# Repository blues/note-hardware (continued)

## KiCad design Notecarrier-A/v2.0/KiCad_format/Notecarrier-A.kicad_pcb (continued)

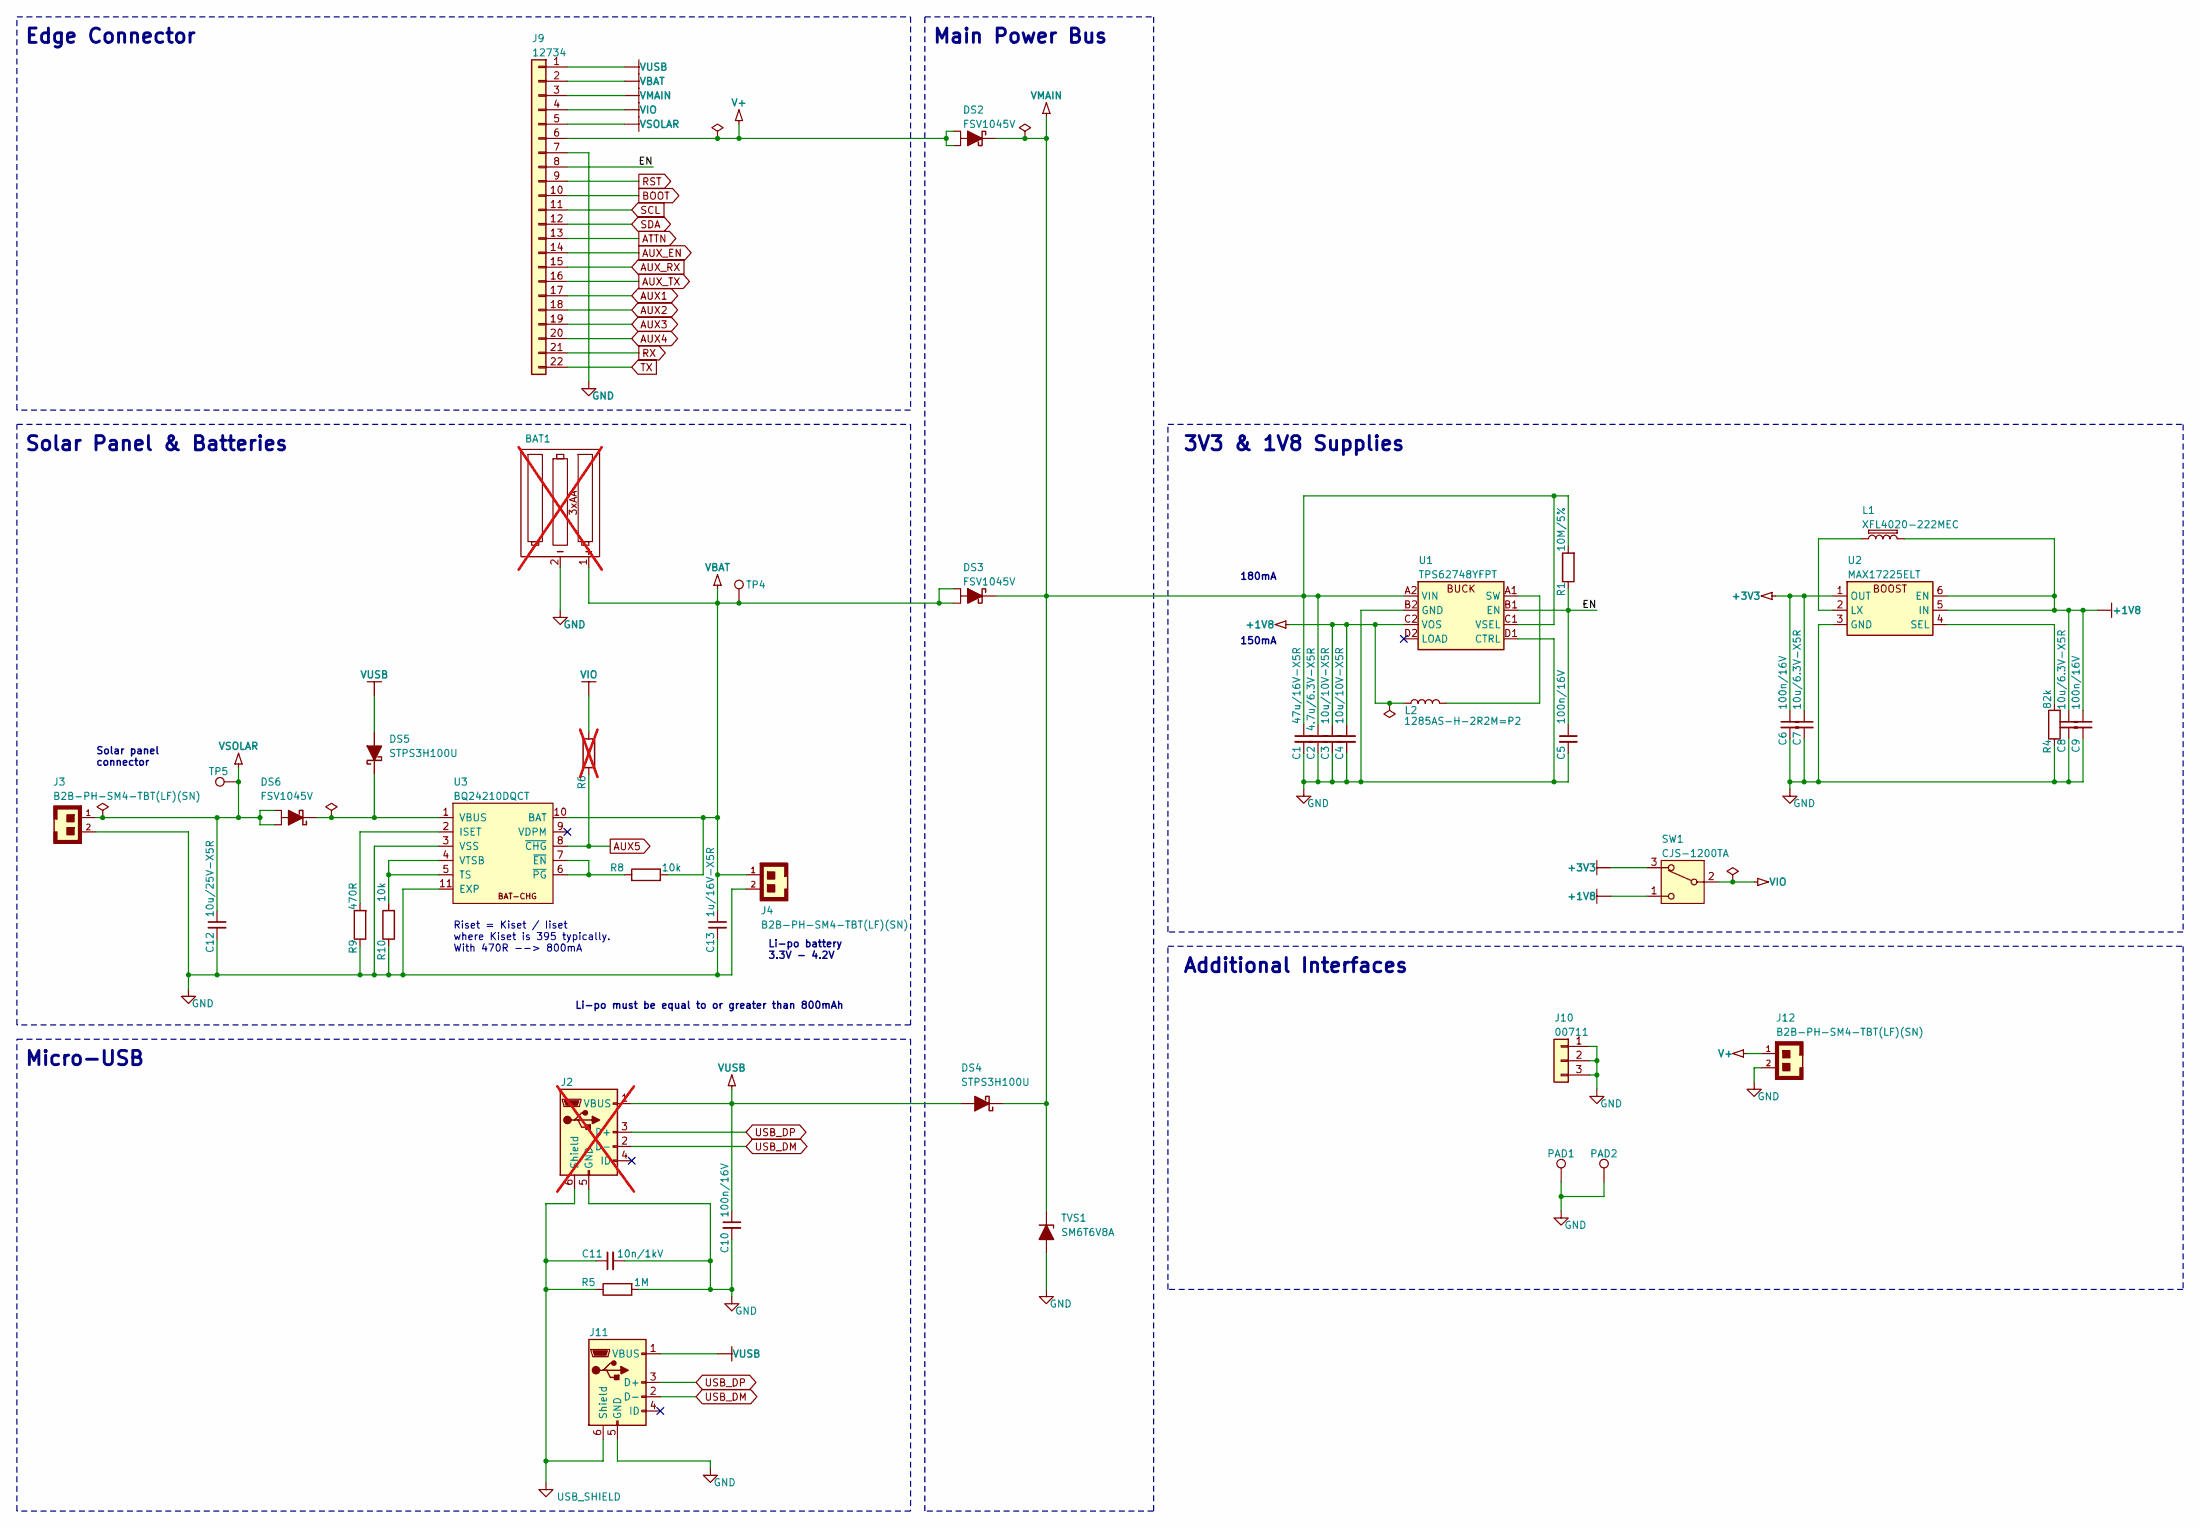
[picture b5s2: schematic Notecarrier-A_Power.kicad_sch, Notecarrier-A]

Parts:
BAT1: NU; BATHLD-2464-NO_MECH; MPN 2464; not fitted
C1: 47u/16V-X5R; CS-C-1206
C2: 4.7u/6.3V-X5R; CS-C-0402
C3, C4: 10u/10V-X5R; CS-C-0603
C5, C6, C9, C10: 100n/16V; CS-C-0402
C7, C8: 10u/6.3V-X5R; CS-C-0402
C11: 10n/1kV; CS-C-1206
C12: 10u/25V-X5R; CS-C-1206
C13: 1u/16V-X5R; CS-C-0402
DS2, DS3, DS6: FSV1045V; TO277-3; MPN FSV1045V
DS4, DS5: STPS3H100U; SMB; MPN STPS3H100U
J2: NU; J-5-0065-FDS-UUSB1051330001_NO-SILK; MPN 1051330001; not fitted
J3, J4, J12: B2B-PH-SM4-TBT(LF)(SN); J-2-0200-MDS-B2B-PH-SM4; MPN B2B-PH-SM4-TBT(LF)(SN)
J9: 12734; J-22-0254-FDT-H0508_EDGE; MPN 12734
J10: 00711; J-3-0254-FDT_H0508; MPN 00711
J11: 10118192-0002LF; J-5-0065-FOS-USB10118192-NOF; MPN 10118192-0002LF
L1: XFL4020-222MEC; LS-XFL4020; MPN XFL4020-222MEC
L2: 1285AS-H-2R2M=P2; LS-0806; MPN 1285AS-H-2R2M=P2
PAD1, PAD2: TPS; PAD-THT-CAS-0100
R1: 10M/5%; RS-0402
R4: 82k; RS-0402
R5: 1M; RS-1206
R6: NU; RS-0402; not fitted
R8, R10: 10k; RS-0402
R9: 470R; RS-0402
SW1: CJS-1200TA; SW_CJS-1200TA_NO-SILK
TP4, TP5: TPS; TPS-SPEA
TVS1: SM6T6V8A; SMB
U1: TPS62748YFPT; XFBGA8; MPN TPS62748YFPT
U2: MAX17225ELT; WDFN6-0200X0200; MPN MAX17225ELT+T
U3: BQ24210DQCT; WSON10-EXP_NO-SILK; MPN BQ24210DQCT

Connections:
+1V8: C3.1, C4.1, C8.1, C9.1, L1.2, L2.2, SW1.1 (C), U1.C2 (VOS), U2.5 (IN), U2.6 (EN)
+3V3: C6.1, C7.1, SW1.3 (A), U2.1 (OUT)
/Power/EN: C5.1, J9.8, R1.1, U1.B1 (EN)
ATTN: J9.13; also elsewhere on the board
AUX1: J9.17; also elsewhere on the board
AUX2: J9.18; also elsewhere on the board
AUX3: J9.19; also elsewhere on the board
AUX4: J9.20; also elsewhere on the board
AUX5: R6.1, U3.8 (~CHG); also elsewhere on the board
AUX_EN: J9.14; also elsewhere on the board
AUX_RX: J9.15; also elsewhere on the board
AUX_TX: J9.16; also elsewhere on the board
BOOT: J9.10; also elsewhere on the board
GND: BAT1.2 (-), C1.2, C2.2, C3.2, C4.2, C5.2, C6.2, C7.2, C8.2, C9.2, C10.2, C11.2, C12.2, C13.2, J2.5 (GND), J3.2, J4.2, J9.7, J10.1, J10.2, J10.3, J11.5 (GND), J12.2, PAD1.1, PAD2.1, R4.1, R5.2, R9.1, R10.1, TVS1.2 (A2), U1.B2 (GND), U1.D1 (CTRL), U2.3 (GND), U3.3 (VSS), U3.11 (EXP); also elsewhere on the board
unnamed: DS5.1 (K), DS6.3 (C), U3.1 (VBUS)
unnamed: C11.1, J2.6 (Shield), J11.6 (Shield), R5.1
unnamed: L2.1, U1.A1 (SW)
unnamed: L1.1, U2.2 (LX)
unnamed: R4.2, U2.4 (SEL)
unnamed: R9.2, U3.2 (ISET)
unnamed: R10.2, U3.4 (VTSB), U3.5 (TS)
unnamed: R8.1, U3.6 (~PG), U3.7 (~EN)
RST: J9.9; also elsewhere on the board
RX: J9.21; also elsewhere on the board
SCL: J9.11; also elsewhere on the board
SDA: J9.12; also elsewhere on the board
TX: J9.22; also elsewhere on the board
USB_DM: J2.2 (D-), J11.2 (D-); also elsewhere on the board
USB_DP: J2.3 (D+), J11.3 (D+); also elsewhere on the board
V+: DS2.1 (A1), DS2.2 (A2), J9.6, J12.1
VBAT: BAT1.1 (+), C13.1, DS3.1 (A1), DS3.2 (A2), J4.1, J9.2, R8.2, TP4.1, U3.10 (BAT)
VIO: J9.4, R6.2, SW1.2 (B); also elsewhere on the board
VMAIN: C1.1, C2.1, DS2.3 (C), DS3.3 (C), DS4.1 (K), J9.3, R1.2, TVS1.1 (A1), U1.A2 (VIN), U1.C1 (VSEL); also elsewhere on the board
VSOLAR: C12.1, DS6.1 (A1), DS6.2 (A2), J3.1, J9.5, TP5.1
VUSB: C10.1, DS4.2 (A), DS5.2 (A), J2.1 (VBUS), J9.1, J11.1 (VBUS); also elsewhere on the board

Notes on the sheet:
Main Power Bus
Riset = Kiset / Iiset where Kiset is 395 typically. With 470R --> 800mA
Micro-USB
Solar Panel & Batteries
150mA
Additional Interfaces
Solar panel connector
Li-po must be equal to or greater than 800mAh
180mA
Li-po battery 3.3V - 4.2V
Edge Connector
3V3 & 1V8 Supplies

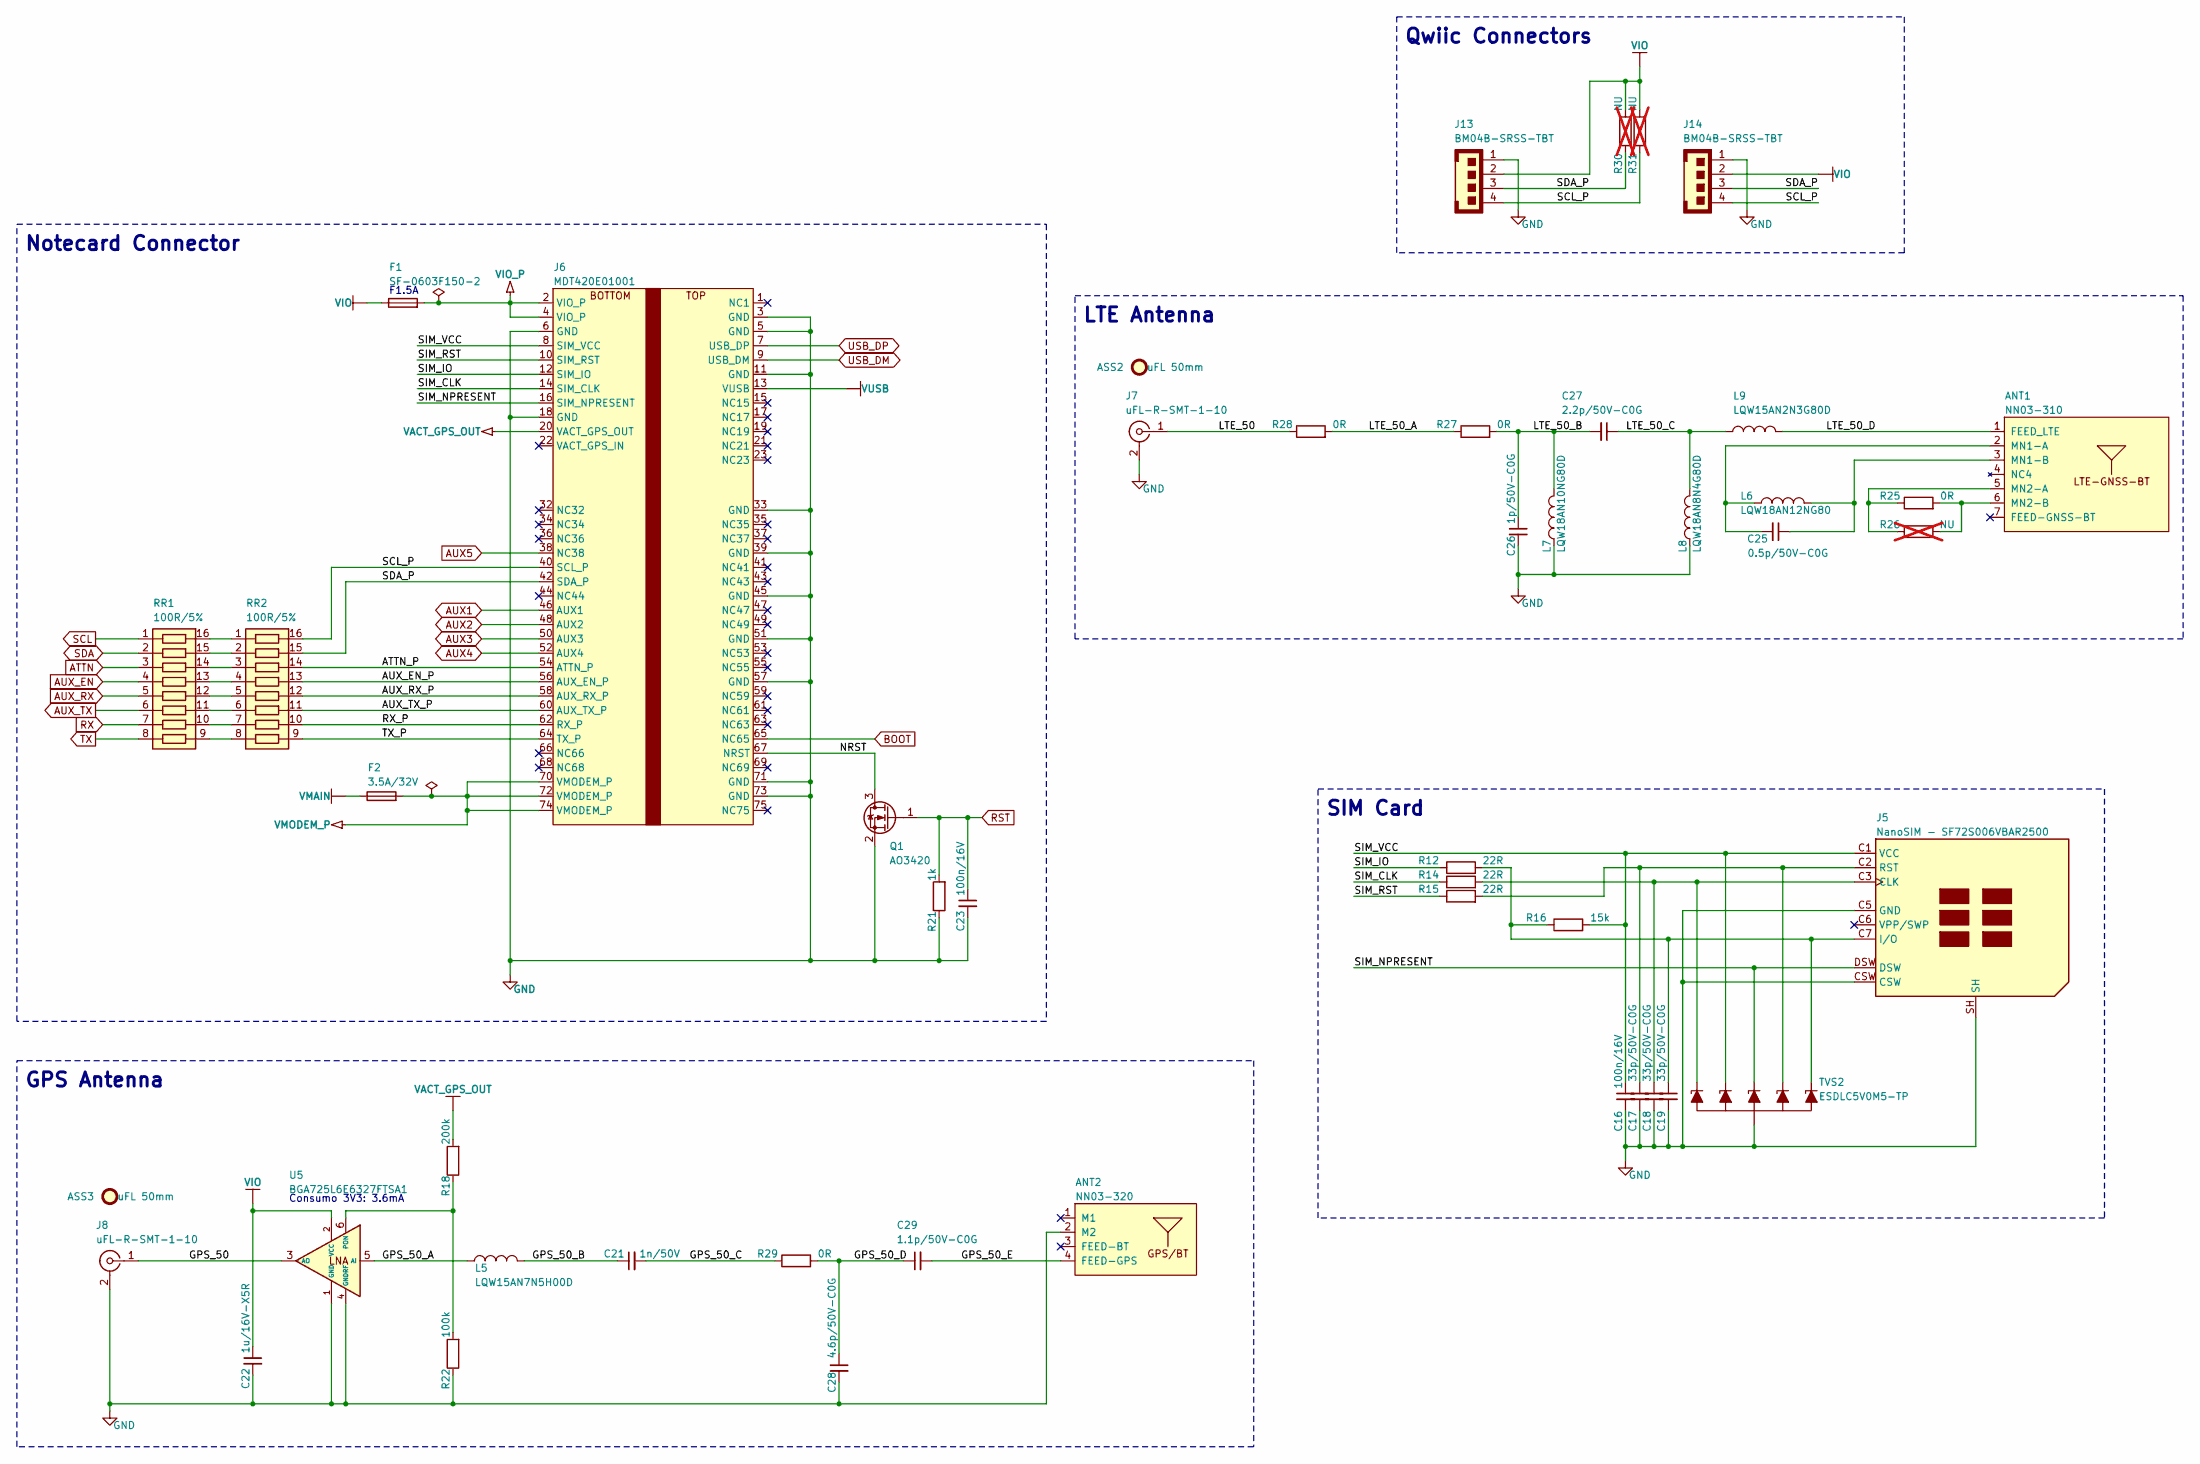
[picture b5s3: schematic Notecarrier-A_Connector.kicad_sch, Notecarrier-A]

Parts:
ANT1: NN03-310; ANT-NN03310-LTE_NO-SILK; MPN NN03-310
ANT2: NN03-320; ANT-NN03320-GPS_NO-SILK; MPN NN03-320
ASS2, ASS3: uFL 50mm
C16, C23: 100n/16V; CS-C-0402
C17, C18, C19: 33p/50V-C0G; CS-C-0402
C21: 1n/50V; FRACTUS-0404_NO-SILK
C22: 1u/16V-X5R; CS-C-0402
C25: 0.5p/50V-C0G; FRACTUS-0404_NO-SILK; MPN GJM1555C1HR50WB01
C26: 1p/50V-C0G; FRACTUS-0404_NO-SILK; MPN GJM1555C1H1R0WB01
C27: 2.2p/50V-C0G; FRACTUS-0404_NO-SILK; MPN GJM1555C1H2R2WB01
C28: 4.6p/50V-C0G; FRACTUS-0404_NO-SILK; MPN GJM1555C1H4R6WB01D
C29: 1.1p/50V-C0G; FRACTUS-0404_NO-SILK; MPN GJM1555C1H1R1WB01D
F1: SF-0603F150-2; FS-0603; MPN SF-0603F150-2
F2: 3.5A/32V; FS-0603; MPN 0603SFV350F/32-2
J5: NanoSIM - SF72S006VBAR2500; J-NANOSIM-SF72S006VBA_NO-FILL; MPN SF72S006VBAR2500
J6: MDT420E01001; J-75-0050-MOS-M2-E_smaller-mask
J7, J8: uFL-R-SMT-1-10; J-3-MDS-UFL_NO-SILK; MPN U.FL-R-SMT-1(10)
J13, J14: BM04B-SRSS-TBT; J-4-0100-MDS-SH_NO-SILK; MPN BM04B-SRSS-TBT(LF)(SN)
L5: LQW15AN7N5H00D; FRACTUS-0404_NO-SILK; MPN LQW15AN7N5H00D
L6: LQW18AN12NG80; FRACTUS-0404_NO-SILK; MPN LQW18AN12NG80
L7: LQW18AN10NG80D; FRACTUS-0404_NO-SILK; MPN LQW18AN10NG80D
L8: LQW18AN8N4G80D; FRACTUS-0404_NO-SILK; MPN LQW18AN8N4G80D
L9: LQW15AN2N3G80D; FRACTUS-0404_NO-SILK; MPN LQW15AN2N3G80D
Q1: AO3420; SOT23
R12, R14, R15: 22R; RS-0603
R16: 15k; RS-0402
R18: 200k; RS-0402
R21: 1k; RS-0402
R22: 100k; RS-0402
R25, R27, R28, R29: 0R; FRACTUS-0404_NO-SILK
R26: NU; FRACTUS-0404_NO-SILK; not fitted
R30, R31: NU; RS-0603; not fitted
RR1, RR2: 100R/5%; RR-8X-1506
TVS2: ESDLC5V0M5-TP; SOT666_NO-SILK
U5: BGA725L6E6327FTSA1; XFDFN6_NO-SILK; MPN BGA725L6E6327FTSA1

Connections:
/Connector/ATTN_P: J6.54 (ATTN_P), RR2.14 (R3_2)
/Connector/AUX_EN_P: J6.56 (AUX_EN_P), RR2.13 (R4_2)
/Connector/AUX_RX_P: J6.58 (AUX_RX_P), RR2.12 (R5_2)
/Connector/AUX_TX_P: J6.60 (AUX_TX_P), RR2.11 (R6_2)
/Connector/GPS_50: J8.1 (In), U5.3 (AO)
/Connector/GPS_50_A: L5.1, U5.5 (AI)
/Connector/GPS_50_B: C21.1, L5.2
/Connector/GPS_50_C: C21.2, R29.1
/Connector/GPS_50_D: C28.1, C29.1, R29.2
/Connector/GPS_50_E: ANT2.4 (FEED-GPS), C29.2
/Connector/LTE_50: J7.1 (In), R28.1
/Connector/LTE_50_A: R27.1, R28.2
/Connector/LTE_50_B: C26.1, C27.2, L7.1, R27.2
/Connector/LTE_50_C: C27.1, L8.1, L9.1
/Connector/LTE_50_D: ANT1.1 (FEED_LTE), L9.2
/Connector/NRST: J6.67 (NRST), Q1.3 (D)
/Connector/RX_P: J6.62 (RX_P), RR2.10 (R7_2)
/Connector/SCL_P: J6.40 (SCL_P), J13.4, J14.4, R31.1, RR2.16 (R1_2)
/Connector/SDA_P: J6.42 (SDA_P), J13.3, J14.3, R30.1, RR2.15 (R2_2)
/Connector/SIM_CLK: J6.14 (SIM_CLK), R14.1
/Connector/SIM_IO: J6.12 (SIM_IO), R12.1
/Connector/SIM_NPRESENT: J5.DSW, J6.16 (SIM_NPRESENT), TVS2.4 (K3)
/Connector/SIM_RST: J6.10 (SIM_RST), R15.1
/Connector/SIM_VCC: C16.1, J5.C1 (VCC), J6.8 (SIM_VCC), R16.2, TVS2.3 (K2)
/Connector/TX_P: J6.64 (TX_P), RR2.9 (R8_2)
ATTN: RR1.3 (R3_1); also elsewhere on the board
AUX1: J6.46 (AUX1); also elsewhere on the board
AUX2: J6.48 (AUX2); also elsewhere on the board
AUX3: J6.50 (AUX3); also elsewhere on the board
AUX4: J6.52 (AUX4); also elsewhere on the board
AUX5: J6.38 (NC38); also elsewhere on the board
AUX_EN: RR1.4 (R4_1); also elsewhere on the board
AUX_RX: RR1.5 (R5_1); also elsewhere on the board
AUX_TX: RR1.6 (R6_1); also elsewhere on the board
BOOT: J6.65 (NC65); also elsewhere on the board
GND: ANT2.2 (M2), C16.2, C17.2, C18.2, C19.2, C22.2, C23.2, C26.2, C28.2, J5.C5 (GND), J5.CSW, J5.SH, J6.3 (GND), J6.5 (GND), J6.6 (GND), J6.11 (GND), J6.18 (GND), J6.33 (GND), J6.39 (GND), J6.45 (GND), J6.51 (GND), J6.57 (GND), J6.71 (GND), J6.73 (GND), J7.2 (Ext), J8.2 (Ext), J13.1, J14.1, L7.2, L8.2, Q1.2 (S), R21.1, R22.1, TVS2.2 (A), U5.1 (GND), U5.4 (GNDRF); also elsewhere on the board
unnamed: ANT1.2 (MN1-A), C25.2, L6.1
unnamed: ANT1.3 (MN1-B), C25.1, L6.2
unnamed: ANT1.5 (MN2-A), R25.1, R26.1
unnamed: ANT1.6 (MN2-B), R25.2, R26.2
unnamed: C18.1, J5.C3 (CLK), R14.2, TVS2.1 (K1)
unnamed: C19.1, J5.C7 (I/O), R12.2, R16.1, TVS2.6 (K5)
unnamed: C17.1, J5.C2 (RST), R15.2, TVS2.5 (K4)
unnamed: RR1.16 (R1_2), RR2.1 (R1_1)
unnamed: RR1.15 (R2_2), RR2.2 (R2_1)
unnamed: RR1.14 (R3_2), RR2.3 (R3_1)
unnamed: RR1.13 (R4_2), RR2.4 (R4_1)
unnamed: RR1.12 (R5_2), RR2.5 (R5_1)
unnamed: RR1.11 (R6_2), RR2.6 (R6_1)
unnamed: RR1.10 (R7_2), RR2.7 (R7_1)
unnamed: RR1.9 (R8_2), RR2.8 (R8_1)
unnamed: R18.1, R22.2, U5.6 (PON)
RST: C23.1, Q1.1 (G), R21.2; also elsewhere on the board
RX: RR1.7 (R7_1); also elsewhere on the board
SCL: RR1.1 (R1_1); also elsewhere on the board
SDA: RR1.2 (R2_1); also elsewhere on the board
TX: RR1.8 (R8_1); also elsewhere on the board
USB_DM: J6.9 (USB_DM); also elsewhere on the board
USB_DP: J6.7 (USB_DP); also elsewhere on the board
VACT_GPS_OUT: J6.20 (VACT_GPS_OUT), R18.2
VIO: C22.1, F1.1, J13.2, J14.2, R30.2, R31.2, U5.2 (VCC); also elsewhere on the board
VIO_P: F1.2, J6.2 (VIO_P), J6.4 (VIO_P)
VMAIN: F2.1; also elsewhere on the board
VMODEM_P: F2.2, J6.70 (VMODEM_P), J6.72 (VMODEM_P), J6.74 (VMODEM_P)
VUSB: J6.13 (VUSB); also elsewhere on the board

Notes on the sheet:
SIM Card
Qwiic Connectors
F1.5A
GPS Antenna
Notecard Connector
Consumo 3V3: 3.6mA
LTE Antenna

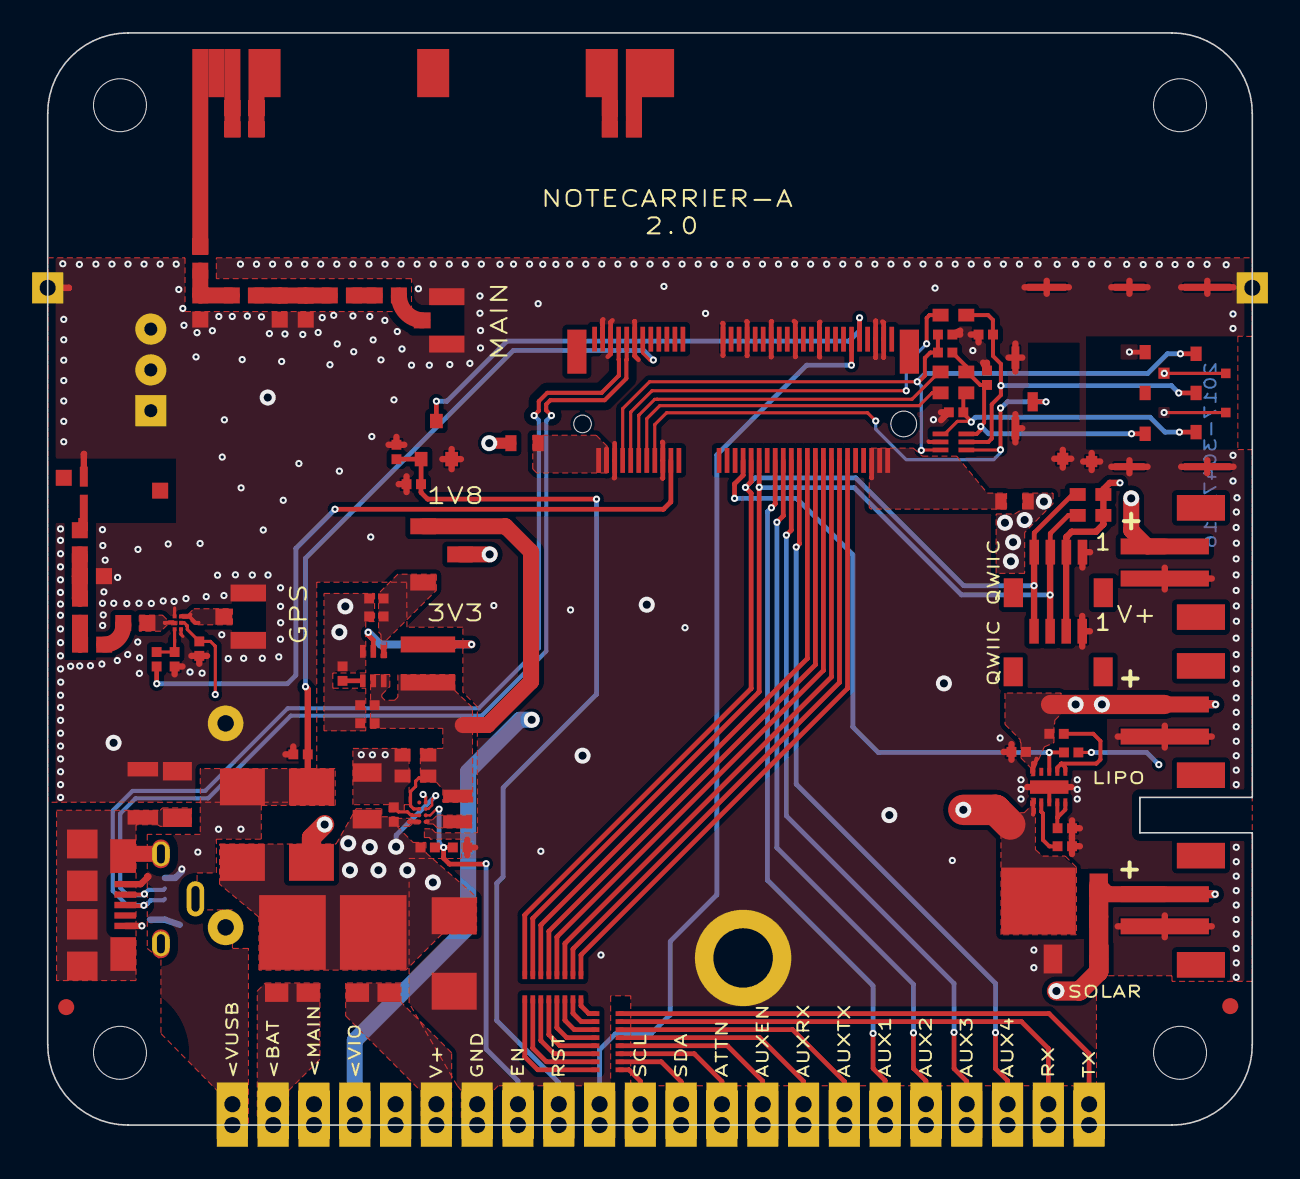
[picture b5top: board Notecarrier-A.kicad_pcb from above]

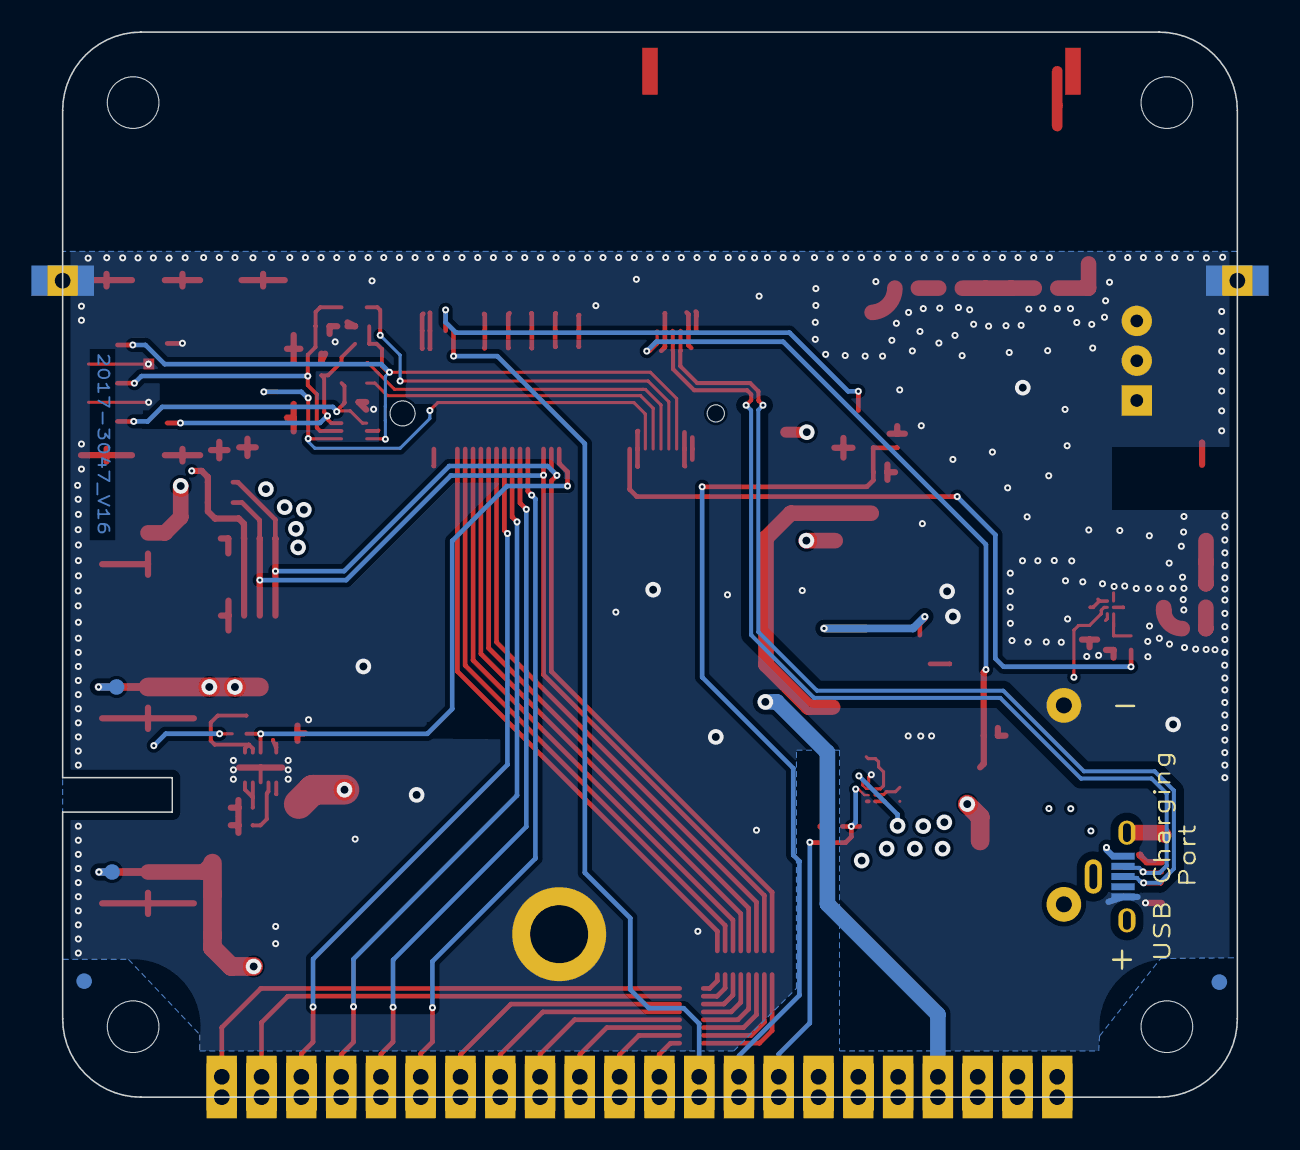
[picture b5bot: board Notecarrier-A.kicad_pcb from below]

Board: 4 copper layers, 75.0 x 68.0 mm, 99 parts (6 on the bottom side), 79 nets.

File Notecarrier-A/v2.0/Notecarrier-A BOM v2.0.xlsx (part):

PROJECT |  | 2017-3047 (NOTECARRIER-M2-AL) |  | Blues Inc
REVISION |  | 16
SCHEMATIC |  | 20173047_NOTECARRIER-M2-AL_V16
DATE |  | 15/11/2021
Item | Quantity | Reference | Part | MPN | Description | Temperature | Type | Package
1 | 1 | ANT1 | NN03-310 | NN03-310 | ANTENNA CHIP LTE/GNSS/BT D=30X3X1 NN03-310 IGNION SMT | -40°..+125° | SMD | ANT-NN03310-LTE
2 | 1 | ANT2 | NN03-320 | NN03-320 | ANTENNA CHIP GPS/BT D=3X7X2 NN03-320 IGNION SMT | -40°..+85° | SMD | ANT-NN03320-GPS
3 | 1 | CS1 | CS V16 4L 35um |  | C.S. NOTECARRIER-M2-AX V16 (75X65)mm 4L/SO/SR ENIG TG150 sp=1.6mm Cu=35um (CONT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 | TG150
4 | 1 | C1 | 47u/16V-X5R | C3216X5R1E476M160AC | CHIP CAP.CER. 47uF 16V 20% X5R 1206 |  | SMD | CS-C-1206
5 | 1 | C2 | 4.7u/6.3V-X5R | JMK105BBJ475MV-F | CHIP CAP.CER. 4.7uF 6.3V 20% X5R 0402 |  | SMD | CS-C-0402
6 | 2 | C3,C4 | 10u/10V-X5R | GRM188R61A106KE69D | CHIP CAP.CER. 10uF 10V 10% X5R 0603 |  | SMD | CS-C-0603
7 | 6 | C5,C6,C9,C10,C16,C23 | 100n/16V | CC0402KRX7R7BB104 | CHIP CAP.CER. 100nF 16V 10% X7R 0402 |  | SMD | CS-C-0402
8 | 2 | C7,C8 | 10u/6.3V-X5R | GRM155R60J106ME44D | CHIP CAP.CER. 10uF 6.3V 20% X5R 0402 | -55°..+85° | SMD | CS-C-0402
9 | 1 | C11 | 10n/1kV | C1206C103KDRACTU | CHIP CAP.CER. 10nF 1000V 10% X7R 1206 |  | SMD | CS-C-1206
10 | 1 | C12 | 10u/25V-X5R | CL31A106KAHNNNE | CHIP CAP.CER. 10uF 25V X5R 10% 1206 |  | SMD | CS-C-1206
11 | 2 | C13,C22 | 1u/16V-X5R | EMK105BJ105MVHF | CHIP CAP.CER. 1uF 16V 10% X5R 0402 |  | SMD | CS-C-0402
12 | 3 | C17,C18,C19 | 33p/50V-C0G | CC0402JRNPO9BN330 | CHIP CAP.CER. 33pF 50V 5% C0G 0402 |  | SMD | CS-C-0402
13 | 1 | C21 | 1n/50V | C0402C102K5RECAUTO | CHIP CAP.CER. 1nF 50V 10% X7R 0402 |  | SMD | FRACTUS-0404
14 | 1 | C25 | 0.5p/50V-C0G | GJM1555C1HR50WB01 | CHIP CAP.CER. 0.5pF 50V ±0.05pF C0G 0603 GJM1555C1HR50WB01 MURATA | -55°..+125° | SMD | FRACTUS-0404
15 | 1 | C26 | 1p/50V-C0G | GJM1555C1H1R0WB01 | CHIP CAP.CER. 1pF 50V ±0.05pF C0G 0603 GJM1555C1H1R0WB01 MURATA | -55°..+125° | SMD | FRACTUS-0404
16 | 1 | C27 | 2.2p/50V-C0G | GJM1555C1H2R2WB01 | CHIP CAP.CER. 2.2pF 50V ±0.05pF C0G 0603 GJM1555C1H2R2WB01 MURATA | -55°..+125° | SMD | FRACTUS-0404
17 | 1 | C28 | 4.6p/50V-C0G | GJM1555C1H4R6WB01D | CHIP CAP.CER. 4.6pF 50V ±0.05pF C0G 0402 GJM1555C1H4R6WB01D MURATA | -55°..+125° | SMD | FRACTUS-0404
18 | 1 | C29 | 1.1p/50V-C0G | GJM1555C1H1R1WB01D | CHIP CAP.CER. 1.1pF 50V ±0.05pF C0G 0402 GJM1555C1H1R1WB01D MURATA | -55°..+125° | SMD | FRACTUS-0404
19 | 3 | DS2,DS3,DS6 | FSV1045V | FSV1045V | SCHOTTKY DIODE 10A 45V FSV1045V TO277-3 SMT | -55°..+150° | SMD | TO277-3
20 | 2 | DS4,DS5 | STPS3H100U | STPS3H100U | SCHOTTKY DIODE 3A 100V STPS3H100U SMB SMT |  | SMD | SMB
21 | 1 | F1 | SF-0603F150-2 | SF-0603F150-2 | RAPID FUSE 1.5A 32V 0603 SF-0603F150-2 BOURNS SMT | -40°..+105° | SMD | FS-0603
22 | 1 | F2 | 3.5A/32V | 0603SFV350F/32-2 | RAPID FUSE 3.5A 32V 0603 0603SFV350F/32-2 LITTELFUSE SMT | -55°..+125° | SMD | FS-0603
23 | 3 | J3,J4,J12 | B2B-PH-SM4-TBT(LF)(SN) | B2B-PH-SM4-TBT(LF)(SN) | CONN. PH 2P M/D P=2 B2B-PH-SM4-TBT(LF)(SN) JST SMT | -25°..+85° | SMD | J-2-0200-MDS-B2B-PH-SM4
24 | 1 | J5 | NanoSIM - SF72S006VBAR2500 | SF72S006VBAR2500 | CONN. NANOSIM 8P F/90° PUSH-PUSH SF72S006VBAR2500 JAE ELECTRONICS SMT | -25°..+85° | SMD | J-NANOSIM-SF72S006VBA
25 | 1 | J6 | MDT420E01001 | MDT420E01001 | CONN. M.2 75P M/90° P=0.5 MDT420E01001 AMPHENOL SMT | -40°..+80° | SMD | J-75-0050-MOS-M2-E
26 | 2 | J7,J8 | uFL-R-SMT-1-10 | U.FL-R-SMT-1(10) | CONN. RF M U.FL-R-SMT-1(10) HIROSE SMT | -40°..+90° | SMD | J-3-MDS-UFL
27 | 1 | J9 | 12734 | 12734 | STRIP 22P F/D P=2.54 H=5.08 12734 4UCON | -55..+105 | THT | J-22-0254-FDT-H0508_EDGE
28 | 1 | J10 | 00711 | 00711 | STRIP 3P F/D P=2.54 H=5.08 00711 4UCON | -55..+105 | THT | J-3-0254-FDT-H0508
29 | 1 | J11 | 10118192-0002LF | 10118192-0002LF | CONN. USB F/90° TIPO MICRO-B C.S. 10118192-0002LF FCI SMT | -30°..+80° | SMD | J-5-0065-FOS-USB10118192-NOF
30 | 2 | J13,J14 | BM04B-SRSS-TBT | BM04B-SRSS-TBT(LF)(SN) | CONN. SH 4P M/D P=1 BM04B-SRSS-TBT(LF)(SN) JST SMT | -25°..+85° | SMD | J-4-0100-MDS-SH
31 | 1 | L1 | XFL4020-222MEC | XFL4020-222MEC | INDUCTOR 2.2 uH 3.1A 20% XFL4020-222MEC COILCRAFT SMT | -40°..+125° | SMD | LS-XFL4020
32 | 1 | L2 | 1285AS-H-2R2M=P2 | 1285AS-H-2R2M=P2 | INDUCTOR 2.2uH 1.5A 20% 0806 1285AS-H-2R2M=P2 MURATA SMT | -40°..+85° | SMD | LS-0806
33 | 1 | L5 | LQW15AN7N5H00D | LQW15AN7N5H00D | INDUCTOR 7.5nH 0.57A 3% A FILO 0402 LQW15AN7N5H00D MURATA SMT | -55°..+125° | SMD | FRACTUS-0404
34 | 1 | L6 | LQW18AN12NG80 | LQW18AN12NG80 | INDUCTOR 12nH 1.5A 2% 0603 LQW18AN12NG80 MURATA SMT | -55°..+125° | SMD | FRACTUS-0404
35 | 1 | L7 | LQW18AN10NG80D | LQW18AN10NG80D | INDUCTOR 10nH 1.6A 2% 0603 LQW18AN10NG80D MURATA SMT | -55°..+125° | SMD | FRACTUS-0404
36 | 1 | L8 | LQW18AN8N4G80D | LQW18AN8N4G80D | INDUCTOR 8.4nH 1.6A 2% 0603 LQW18AN8N4G80D MURATA SMT | -55°..+125° | SMD | FRACTUS-0404
37 | 1 | L9 | LQW15AN2N3G80D | LQW15AN2N3G80D | INDUCTOR 2.3nH 2.53A 2% 0402 LQW15AN2N3G80D MURATA SMT | -55°..+125° | SMD | FRACTUS-0404
38 | 1 | OBJ1 | 9774025151R | 9774025151R | STEEL SPACER 5.1X2.5 9774025151R W.E SMT |  | FAE | SMD
39 | 1 | Q1 | AO3420 | AO3420 | TRANSISTOR MOSFET N AO3420 SOT-23 ALPHA-OMEGA SMT | -55°..+150° | SMD | SOT23
40 | 2 | RR1,RR2 | 100R/5% | CAY16-101J8LF | ARRAY CHIP RES. 8R sing. 100R 5% 1506 CAY16-101J8LF BOURNS SMT | -55°..+125° | SMD | RR-8X-1506
41 | 1 | R1 | 10M/5% | SG73S1ETTP106J | CHIP RES. 10M 0402 1/8W 5% | -55°..+125° | SMD | RS-0402
42 | 1 | R4 | 82k | CRCW040282K0FKTDBC | CHIP RES. 82K 0402 1/16W 1% | -55°..+155° | SMD | RS-0402
43 | 1 | R5 | 1M | CRCW12061M00FKTABC | CHIP RES. 1M 1206 1/4W 1% |  | SMD | RS-1206
44 | 2 | R8,R10 | 10k | RC0402FR-0710KL | CHIP RES. 10K 0402 1/16W 1% | -55°..+125° | SMD | RS-0402
45 | 1 | R9 | 470R | CRCW0402470RFKTDBC | CHIP RES. 470R 0402 1/16W 1% |  | SMD | RS-0402
46 | 3 | R12,R14,R15 | 22R | RC0603FR-0722RL | CHIP RES. 22R 0603 1/16W 1% |  | SMD | RS-0603
47 | 1 | R16 | 15k | RC0402FR-0715KL | CHIP RES. 15K 0402 1/16W 1% | -55°..+155° | SMD | RS-0402
48 | 1 | R18 | 200k | RC0402FR-07200KL | CHIP RES. 200K 0402 1/16W 1% |  | SMD | RS-0402
49 | 1 | R21 | 1k | RC0402FR-071KL | CHIP RES. 1K 0402 1/16W 1% | -55°..+155° | SMD | RS-0402
50 | 1 | R22 | 100k | RC0402FR-07100KL | CHIP RES. 100K 0402 1/16W 1% |  | SMD | RS-0402
51 | 4 | R25,R27,R28,R29 | 0R | RC0603JR-070RL | CHIP RES. 0R 0603 1/16W 1% | -55°..+150° | SMD | FRACTUS-0404
52 | 1 | SW1 | CJS-1200TA | CJS-1200TA | SWITCH SLIDE ON-ON DA C.S. CJS-1200TA NIDEC COPAL ELECTRONICS SMT | -40°..+85° | SMD | SW-CJS1200TA
53 | 1 | TVS1 | SM6T6V8A | SM6T6V8A | DIODE TVS TRANSIL UNIDIR. 600W 6.8V SM6T6V8A SMB SMT |  | SMD | SMB
54 | 1 | TVS2 | ESDLC5V0M5-TP | ESDLC5V0M5-TP | DIODE TVS TRANSIL UNIDIR. 20W 5V ESDLC5V0M5-TP SOT563 SMT | -65°..+150° | SMD | SOT666
55 | 1 | U1 | TPS62748YFPT | TPS62748YFPT | I.C. TPS62748YFPT TEXAS DSBGA8 SMT | -40°..+85° | SMD | XFBGA8
56 | 1 | U2 | MAX17225ELT | MAX17225ELT+T | I.C. MAX17225ELT+T MAXIM W-DFN6 SMT | -40°..+85° | SMD | WDFN6-0200X0200
57 | 1 | U3 | BQ24210DQCT | BQ24210DQCT | I.C. BQ24210DQCT WSON10 TEXAS SMT | -40°..+85° | SMD | WSON10-EXP
58 | 1 | U5 | BGA725L6E6327FTSA1 | BGA725L6E6327FTSA1 | I.C. BGA725L6E6327FTSA1 INFINEON TSLP-6 SMT | -40°..+125° | SMD | XFDFN6
 | 82
MECHANICAL
1 | 1 | ASS1 | PHILIPS SCREW | 179-5691 | SCREW TCEI 2.5X4 INOX DIN 7985 PHILIPS
2 | 2 | ASS2,ASS3 | uFL 50mm | 415-0086-050 | COAX CABLE uFl-uFl 415-0086-050 HIROSE CINCH CONNECTIVITY SOLUTIONS JOHNSON
3 | 1 |  |  | MGKWKB500M | PINK ANTISTATIC ESD BAG 76X130mm MGKWKB500M
4 | 1 |  |  |  | BLUES LABEL
NOT MOUNTED
1 | 1 | BAT1 | NU | 2464 | BATTERY HOLDER 2464 KEYSTONE |  | THT | BATHLD-2464-NO_MECH
2 | 4 | FID1,FID2,FID3,FID4 | TPS |  | FIDUCIAL |  | SMD | FIDUCIAL
3 | 1 | J2 | NU | 1051330001 | CONN. USB F/D TIPO MICRO-B C.S. 1051330001 MOLEX SMT | -30°..+85° | SMD | J-5-0065-FDS-UUSB1051330001
4 | 2 | PAD1,PAD2 | TPS |  | CASTELLATED EDGE VIAS |  | THT | PAD-THT-CAS-0100
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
